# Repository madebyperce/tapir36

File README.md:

# tapir36
Minimally MX-spaced reversible ergo split board

## Updates
Rev 1.1 has: 
* Updated diode footprint silkscreen -- easier to understand diode direction
* Updated MCU silkscreen -- easier to understand which set of holes to solder
* Moved MCU and TRRS female jack receiver up to resolve desing issue of PCB in way of TRRS jack
* Added reset switch pads
* Simplified Tapir art 
* Increased font size of text

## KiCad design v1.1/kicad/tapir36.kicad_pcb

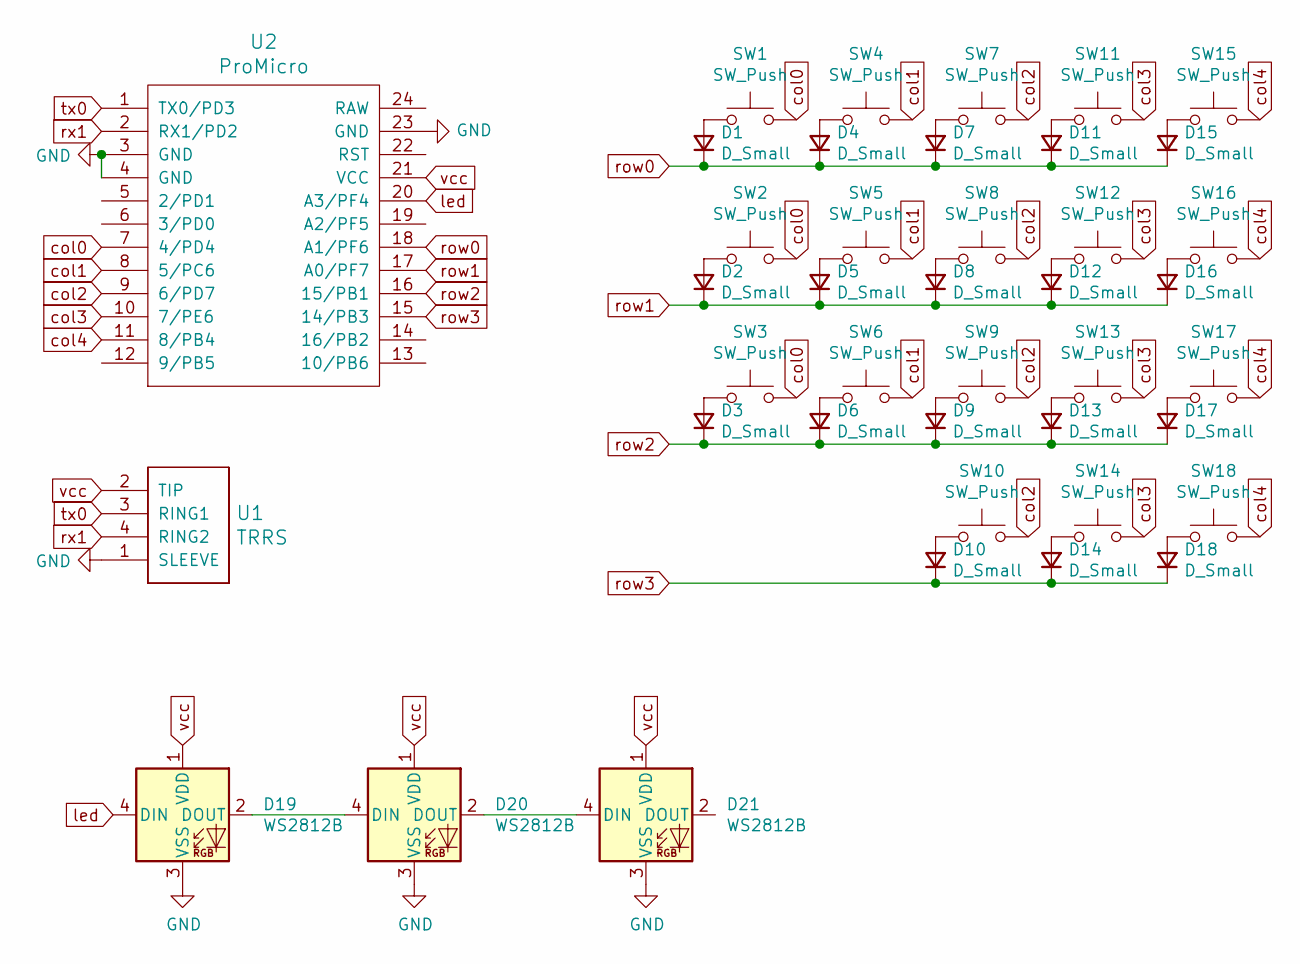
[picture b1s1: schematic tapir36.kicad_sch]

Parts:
D1, D2, D3, D4, D5, D6, D7, D8, D9, D10, D11, D12, D13, D14, D15, D16, D17, D18: D_Small; D_MiniMELF-DoubleSide
D19, D20, D21: WS2812B; LED_WS2812B_PLCC4_5.0x5.0mm_P3.2mm
SW1, SW2, SW3, SW4, SW5, SW6, SW7, SW8, SW9, SW10, SW11, SW12, SW13, SW14, SW15, SW16, SW17, SW18: SW_Push; MX-reversible-min-spacing
U1: TRRS; TRRS-PJ-320A-dual_slim
U2: ProMicro; ReversibleProMicro

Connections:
GND: D19.3 (VSS), D20.3 (VSS), D21.3 (VSS), U1.1 (SLEEVE), U2.3 (GND), U2.4 (GND), U2.23 (GND); also elsewhere on the board
unnamed: D1.2 (A), SW1.1
unnamed: D2.2 (A), SW2.1
unnamed: D3.2 (A), SW3.1
unnamed: D4.2 (A), SW4.1
unnamed: D5.2 (A), SW5.1
unnamed: D6.2 (A), SW6.1
unnamed: D7.2 (A), SW7.1
unnamed: D8.2 (A), SW8.1
unnamed: D9.2 (A), SW9.1
unnamed: D10.2 (A), SW10.1
unnamed: D11.2 (A), SW11.1
unnamed: D12.2 (A), SW12.1
unnamed: D13.2 (A), SW13.1
unnamed: D14.2 (A), SW14.1
unnamed: D15.2 (A), SW15.1
unnamed: D16.2 (A), SW16.1
unnamed: D17.2 (A), SW17.1
unnamed: D18.2 (A), SW18.1
unnamed: D19.2 (DOUT), D20.4 (DIN)
unnamed: D20.2 (DOUT), D21.4 (DIN)
col0: SW1.2, SW2.2, SW3.2, U2.7 (4/PD4)
col1: SW4.2, SW5.2, SW6.2, U2.8 (5/PC6)
col2: SW7.2, SW8.2, SW9.2, SW10.2, U2.9 (6/PD7)
col3: SW11.2, SW12.2, SW13.2, SW14.2, U2.10 (7/PE6)
col4: SW15.2, SW16.2, SW17.2, SW18.2, U2.11 (8/PB4)
led: D19.4 (DIN), U2.20 (A3/PF4)
row0: D1.1 (K), D4.1 (K), D7.1 (K), D11.1 (K), D15.1 (K), U2.18 (A1/PF6)
row1: D2.1 (K), D5.1 (K), D8.1 (K), D12.1 (K), D16.1 (K), U2.17 (A0/PF7)
row2: D3.1 (K), D6.1 (K), D9.1 (K), D13.1 (K), D17.1 (K), U2.16 (15/PB1)
row3: D10.1 (K), D14.1 (K), D18.1 (K), U2.15 (14/PB3)
rx1: U1.4 (RING2), U2.2 (RX1/PD2)
tx0: U1.3 (RING1), U2.1 (TX0/PD3)
vcc: D19.1 (VDD), D20.1 (VDD), D21.1 (VDD), U1.2 (TIP), U2.21 (VCC)

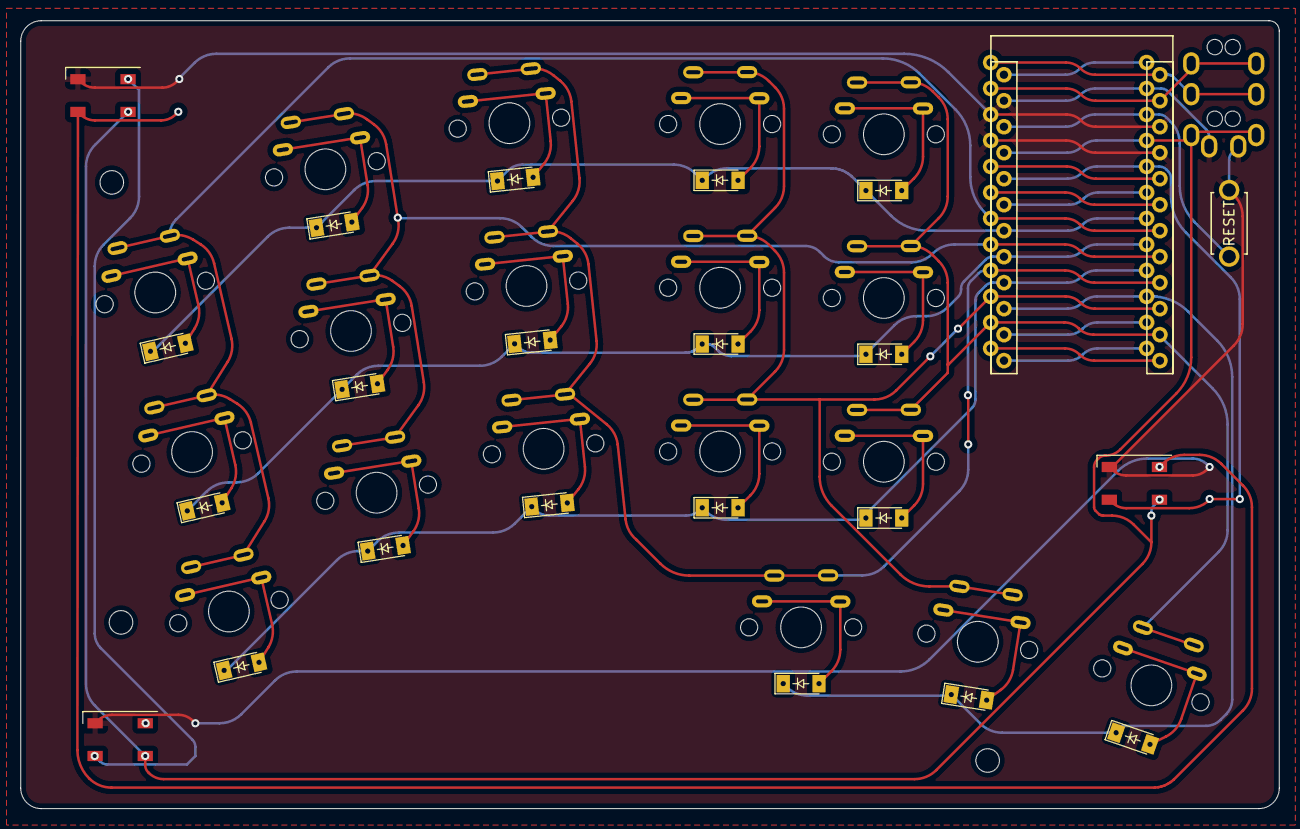
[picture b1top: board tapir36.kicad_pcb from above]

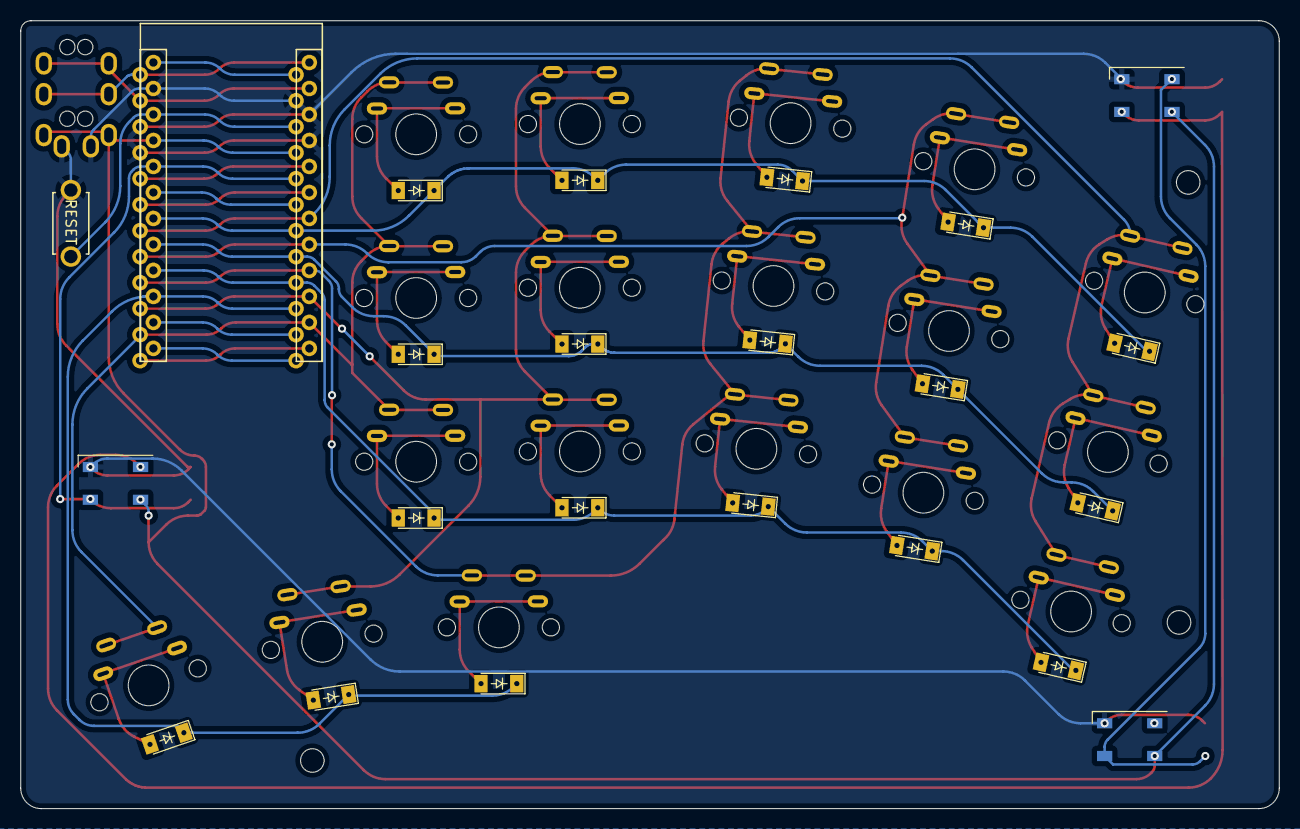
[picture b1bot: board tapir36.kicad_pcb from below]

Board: 2 copper layers, 123.0 x 77.0 mm, 43 parts (21 on the bottom side), 34 nets.

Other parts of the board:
RSW1: SW_PUSH; ResetSW
Ref**: Val**; thread_m2

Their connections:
GND: RSW1.1; also elsewhere on the board

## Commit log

2021-08-10 update with proper naming
2021-08-10 Update README.md
    Add photos to readme
2021-08-10 cleanup
2021-08-10 add lil tapir guy
2021-08-10 typo
2021-08-10 fix vcc flags lmao
2021-08-26 updoot
2021-08-26 Add real photo
2021-08-28 add qmk firmware
2021-09-09 add case
